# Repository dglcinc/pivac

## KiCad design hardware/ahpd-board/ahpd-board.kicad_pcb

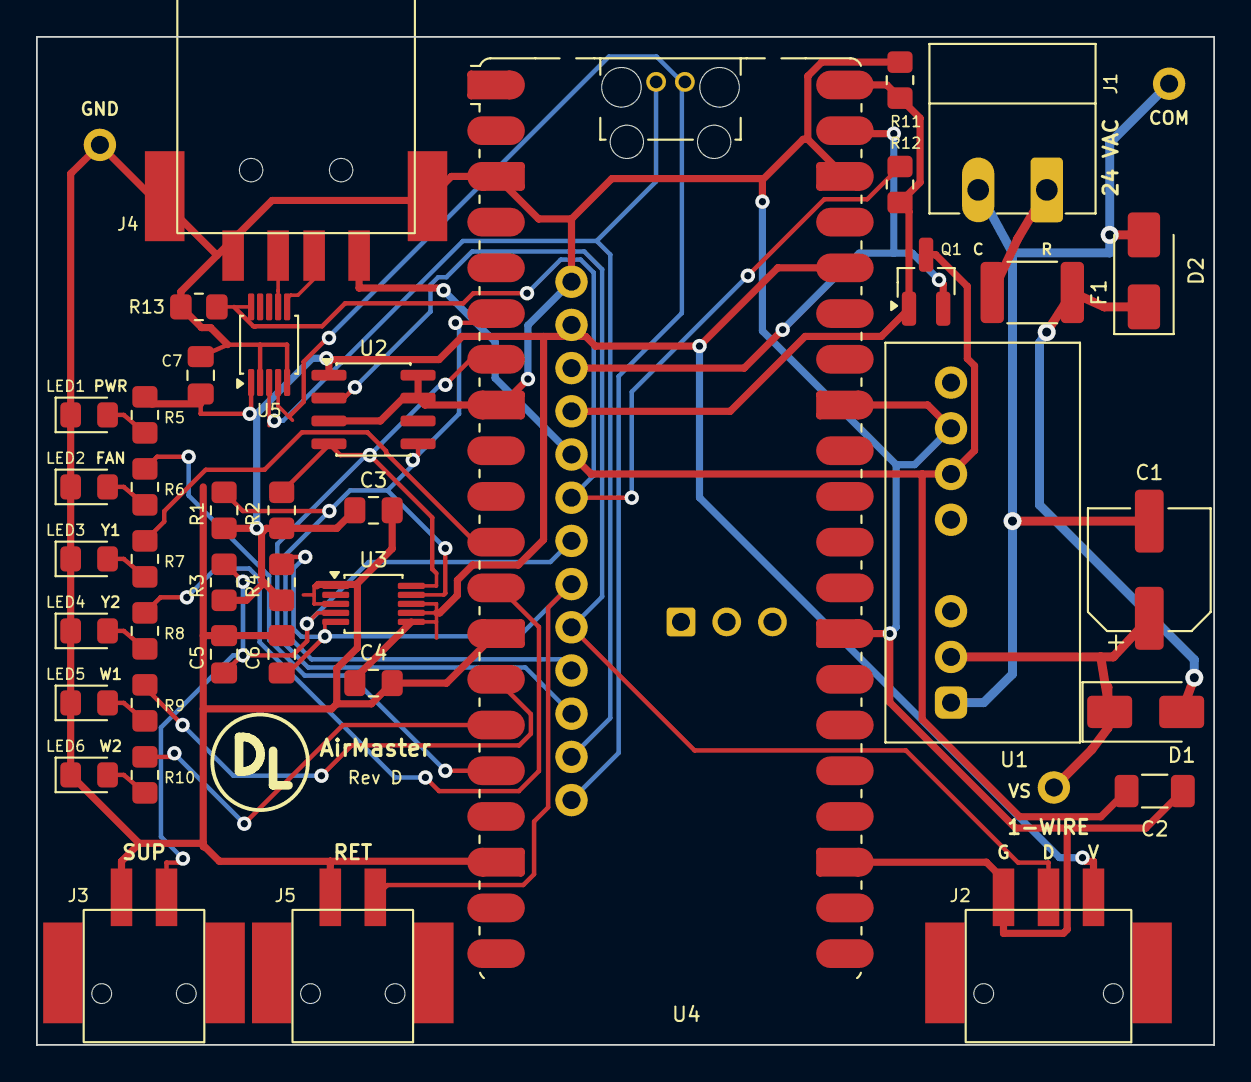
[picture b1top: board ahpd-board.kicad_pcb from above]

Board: 2 copper layers, 65.4 x 56.0 mm, 56 parts (0 on the bottom side), 30 nets.

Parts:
C1: 47u 50V; CP_Elec_6.3x7.7
C2: 100u 6.3V; C_1206_3216Metric_Pad1.33x1.80mm_HandSolder
C3, C4, C5, C6, C7: 100n; C_0805_2012Metric_Pad1.18x1.45mm_HandSolder
D1: M7; D_SMA
D2: SMAJ43CA; D_SMA
F1: PTC 0.2A; Fuse_1812_4532Metric_Pad1.30x3.40mm_HandSolder
J1: 3.81 mm 2-pin 24VAC; PhoenixContact_MC_1,5_2-G-3.81_1x02_P3.81mm_Horizontal
J2: PTSM 0,5/3-HH-2,5-SMD; PTSM_0.5_3-HH-2.5-SMD
J3, J5: PTSM 0,5/2-HH-2,5-SMD; PTSM_0.5_2-HH-2.5-SMD
J4: U-A-24SS-W-1; USB_A_HRO_U-A-24SS-W-1
LED1: 0805 green; LED_0805_2012Metric_Pad1.15x1.40mm_HandSolder
LED2: 0805 yellow; LED_0805_2012Metric_Pad1.15x1.40mm_HandSolder
LED3, LED4: 0805 blue; LED_0805_2012Metric_Pad1.15x1.40mm_HandSolder
LED5, LED6: 0805 red; LED_0805_2012Metric_Pad1.15x1.40mm_HandSolder
Q1: DMG2305UX-7; SOT-23_Handsoldering
R1, R2: 4k7; R_0805_2012Metric_Pad1.20x1.40mm_HandSolder
R3, R4: 10k0 0.1%; R_0805_2012Metric_Pad1.20x1.40mm_HandSolder
R5, R6, R7, R8, R9, R10: 220R; R_0805_2012Metric_Pad1.20x1.40mm_HandSolder
R11: 100k; R_0805_2012Metric_Pad1.20x1.40mm_HandSolder
R12: 22k; R_0805_2012Metric_Pad1.20x1.40mm_HandSolder
R13: 33k; R_0805_2012Metric_Pad1.20x1.40mm_HandSolder
TP1: VS; TestHole
TP2: COM; TestHole
TP3, TP4: GND; TestHole
TP5: 3V3; TestHole
TP6: VSYS; TestHole
TP7: VBUS; TestHole
TP8: +5V; TestHole
TP9: OE; TestHole
TP10: SUP; TestHole
TP11: RET; TestHole
TP12: OW; TestHole
TP13: SDA; TestHole
TP14: SCL; TestHole
TP15: PD+; TestHole
TP16: PD-; TestHole
U1: URB4805S-3WR3; TMR3WI_TMR12WI_SIP-8
U2: DS2482S-100+; SOIC-8_3.9x4.9mm_P1.27mm
U3: ADS1115IDGS; MSOP-10_3x3mm_P0.5mm
U4: Pico W SC0918; RaspberryPi_Pico_W_SMD_HandSolder
U5: FSUSB42MUX; MSOP-10_3x3mm_P0.5mm

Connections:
3V3: C3.1, C4.1, C7.1, J2.1, R1.1, R2.1, R3.1, R4.1, R5.2, TP5.1, U2.1, U3.6, U3.7, U3.8, U4.36, U5.1
+5V: C2.1, J4.1, Q1.3, TP8.1, U1.6
ACF: D1.2, D2.1, F1.2
ACR: F1.1, J1.1
A_LED1: LED1.2, R5.1
A_LED2: LED2.2, R6.1
A_LED3: LED3.2, R7.1
A_LED4: LED4.2, R8.1
A_LED5: LED5.2, R9.1
A_LED6: LED6.2, R10.1
COM: C1.2, D2.2, J1.2, TP2.1, U1.1
D+: J4.3, U5.7
D-: J4.2, U5.6
GND: C2.2, C3.2, C4.2, C5.2, C6.2, C7.2, J2.3, J3.2, J4.4, J4.S, J5.2, LED1.1, LED2.1, LED3.1, LED4.1, LED5.1, LED6.1, R11.2, R13.2, TP3.1, TP4.1, U1.7, U2.3, U2.7, U2.8, U3.1, U3.3, U4.3, U4.8, U4.13, U4.18, U4.23, U4.28, U4.33, U4.38, U5.2, U5.5
L_FAN: R6.2, U4.16
L_W1: R9.2, U4.14
L_W2: R10.2, U4.15
L_Y1: R7.2, U4.11
L_Y2: R8.2, U4.12
OE: R12.2, R13.1, TP9.1, U5.10
OW: J2.2, TP12.1, U2.2
PD+: TP15.1, U4.TP3, U5.3
PD-: TP16.1, U4.TP2, U5.4
RET: C6.1, J5.1, R4.2, TP11.1, U3.5
SCL: R2.2, TP14.1, U2.4, U3.10, U4.7
SDA: R1.2, TP13.1, U2.5, U3.9, U4.6
SUP: C5.1, J3.1, R3.2, TP10.1, U3.4
VBUS: Q1.1, R11.1, R12.1, TP7.1, U4.40
VS: C1.1, D1.1, TP1.1, U1.2
VSYS: Q1.2, TP6.1, U4.39

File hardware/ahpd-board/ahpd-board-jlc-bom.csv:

Comment,Designator,Footprint,LCSC Part #
UUD1H470MCL1GS 47uF 50V,C1,CP_Elec_6.3x7.7,C445256
CL31A107MQHNNNE 100uF 6.3V 1206,C2,C_1206_3216Metric_Pad1.33x1.80mm_HandSolder,C15008
CC0805KRX7R9BB104 100nF 50V 0805,"C3,C4,C5,C6,C7",C_0805_2012Metric_Pad1.18x1.45mm_HandSolder,C49678
M7 1N4007 SMA,D1,D_SMA,C95872
SMAJ43CA,D2,D_SMA,C223990
1812L020/60DR,F1,Fuse_1812_4532Metric_Pad1.30x3.40mm_HandSolder,C315900
"1803277 MC 1,5/2-G-3,81",J1,"PhoenixContact_MC_1,5_2-G-3.81_1x02_P3.81mm_Horizontal",C480537
"1778777 PTSM 0,5/3-HH-2,5-SMD",J2,PTSM_0.5_3-HH-2.5-SMD,C3583902
"1778764 PTSM 0,5/2-HH-2,5-SMD","J3,J5",PTSM_0.5_2-HH-2.5-SMD,C5149246
U-A-24SS-W-1 USB-A,J4,USB_A_HRO_U-A-24SS-W-1,C283549
KT-0805G green,LED1,LED_0805_2012Metric_Pad1.15x1.40mm_HandSolder,C2297
KT-0805Y yellow,LED2,LED_0805_2012Metric_Pad1.15x1.40mm_HandSolder,C2296
KT-0805B blue,"LED3,LED4",LED_0805_2012Metric_Pad1.15x1.40mm_HandSolder,C2293
NCD0805R1 red,"LED5,LED6",LED_0805_2012Metric_Pad1.15x1.40mm_HandSolder,C84256
DMG2305UX-7,Q1,SOT-23_Handsoldering,C150470
4.7k 1% 0805,"R1,R2",R_0805_2012Metric_Pad1.20x1.40mm_HandSolder,C17673
RT0805BRD0710KL 10k 0.1% 0805,"R3,R4",R_0805_2012Metric_Pad1.20x1.40mm_HandSolder,C110775
220R 1% 0805,"R5,R6,R7,R8,R9,R10",R_0805_2012Metric_Pad1.20x1.40mm_HandSolder,C17557
100k 1% 0805,R11,R_0805_2012Metric_Pad1.20x1.40mm_HandSolder,C149504
22k 1% 0805,R12,R_0805_2012Metric_Pad1.20x1.40mm_HandSolder,C17560
33k 1% 0805,R13,R_0805_2012Metric_Pad1.20x1.40mm_HandSolder,C17633
URB4805S-3WR3,U1,TMR3WI_TMR12WI_SIP-8,C20198635
DS2482S-100+T&R,U2,SOIC-8_3.9x4.9mm_P1.27mm,C143306
ADS1115IDGSR,U3,MSOP-10_3x3mm_P0.5mm,C37593
Raspberry Pi Pico W,U4,RaspberryPi_Pico_W_SMD_HandSolder,C7203003
FSUSB42MUX,U5,MSOP-10_3x3mm_P0.5mm,C11355

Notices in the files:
hardware/ahpd-board/ahpd-board.kicad_pcb:
© 2026 David Lewis
CC BY-NC 4.0
